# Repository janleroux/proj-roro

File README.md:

# RORO10

## Overview
The LERU Roro v1.0 is a small wireless transceiver module offers a comprehensive mix of long range, low power consumption and secure data transmission.It is designed to facilitate developers to quickly move the same platform they use for prototyping to industrial level LoRa and IoT solutions. It offers all the core functions that will solve 99% of the requirements to turn an idea to reality. It is easy to program, create and connect your things everywhere. 

The Roro wireless part is based on a RFM95 module which allows the user to send data and reach extremely long ranges at low data-rates. It provides ultra-long range spread spectrum communication and high interference immunity whilst minimising current consumption. It targets professional wireless sensor network applications such as irrigation systems, smart metering, smart cities, smartphone detection, building automation, to name a few.

Roro's mcu part use an ESP32 module from Espressif Systems. The ESP32 is a well known, widely used ultra-low-power microcontroller that incorporate connectivity options such as Wi-Fi and Bluetooth. It offers two CPU cores that can be individually controlled,and the CPU clock frequency is adjustable from 80 MHz to 240 MHz. The chip also has a low-powerco-processor that can be used instead of the CPU to save power while performing tasks that do not require muchcomputing power, such as monitoring of peripherals. ESP32 integrates a rich set of peripherals, ranging fromcapacitive touch sensors, Hall sensors, SD card interface, Ethernet, high-speed SPI, UART, I²S and I²C

[Roro Wiki](https://github.com/janleroux/leru-roro/wiki)

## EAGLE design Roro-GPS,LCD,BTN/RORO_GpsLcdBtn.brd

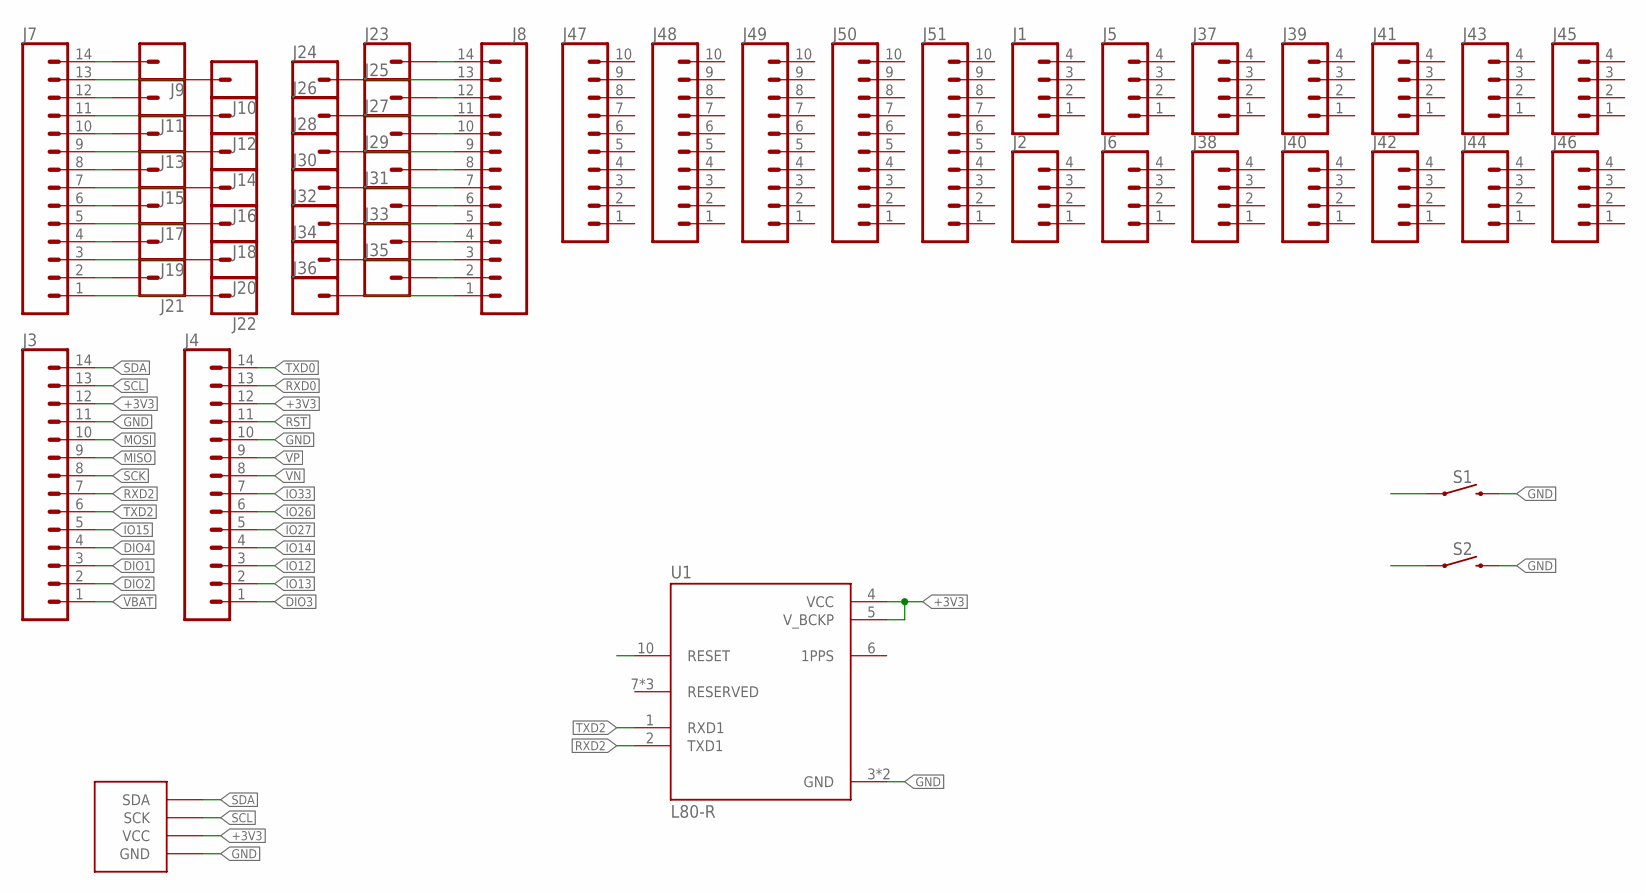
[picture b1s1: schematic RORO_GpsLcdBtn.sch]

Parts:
J1, J2, J5, J6, J37, J38, J39, J40, J41, J42, J43, J44, J45, J46: CONN_041X04_NO_SILK; 1X04_NO_SILK
J3, J4, J7, J8: CONN_14NO_SILK; 1X14_NO_SILK
J9, J10, J11, J12, J13, J14, J15, J16, J17, J18, J19, J20, J21, J22, J23, J24, J25, J26, J27, J28, J29, J30, J31, J32, J33, J34, J35, J36: CONN_01PTH_NO_SILK_KIT; 1X01NS_KIT
J47, J48, J49, J50, J51: CONN_10NO_SILK_PTH_FEMALE; 1X10_NO_SILK
S1, S2: MOMENTARY-SWITCH-SPST-SMD-6.0X3.5MM; TACTILE_SWITCH_SMD_6.0X3.5MM
U1: L80-R; XCVR_L80-R
U$1: 128X64_I2COLED

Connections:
+3V3: J3.12, J4.12, U1.4 (VCC), U1.5 (V_BCKP), U$1.P$3 (VCC)
DIO1: J3.3
DIO2: J3.2
DIO3: J4.1
DIO4: J3.4
GND: J3.11, J4.10, S1.2, S2.2, U1.3 (GND), U1.12 (GND), U$1.P$4 (GND)
IO12: J4.3
IO13: J4.2
IO14: J4.4
IO15: J3.5
IO26: J4.6
IO27: J4.5
IO33: J4.7
MISO: J3.9
MOSI: J3.10
unnamed: J7.14, J9.1
unnamed: J7.13, J10.1
unnamed: J7.12, J11.1
unnamed: J7.11, J12.1
unnamed: J7.10, J13.1
unnamed: J7.9, J14.1
unnamed: J7.8, J15.1
unnamed: J7.7, J16.1
unnamed: J7.6, J17.1
unnamed: J7.5, J18.1
unnamed: J7.4, J19.1
unnamed: J7.3, J20.1
unnamed: J7.2, J21.1
unnamed: J7.1, J22.1
unnamed: J8.14, J23.1
unnamed: J8.13, J24.1
unnamed: J8.12, J25.1
unnamed: J8.11, J26.1
unnamed: J8.10, J27.1
unnamed: J8.9, J28.1
unnamed: J8.8, J29.1
unnamed: J8.7, J30.1
unnamed: J8.6, J31.1
unnamed: J8.5, J32.1
unnamed: J8.4, J33.1
unnamed: J8.3, J34.1
unnamed: J8.2, J35.1
unnamed: J8.1, J36.1
RST: J4.11
RXD0: J4.13
RXD2: J3.7, U1.2 (TXD1)
SCK: J3.8
SCL: J3.13, U$1.P$2 (SCK)
SDA: J3.14, U$1.P$1 (SDA)
TXD0: J4.14
TXD2: J3.6, U1.1 (RXD1)
VBAT: J3.1
VN: J4.8
VP: J4.9

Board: 2 copper layers, 55 parts (0 on the bottom side), 34 nets, no tracks yet.

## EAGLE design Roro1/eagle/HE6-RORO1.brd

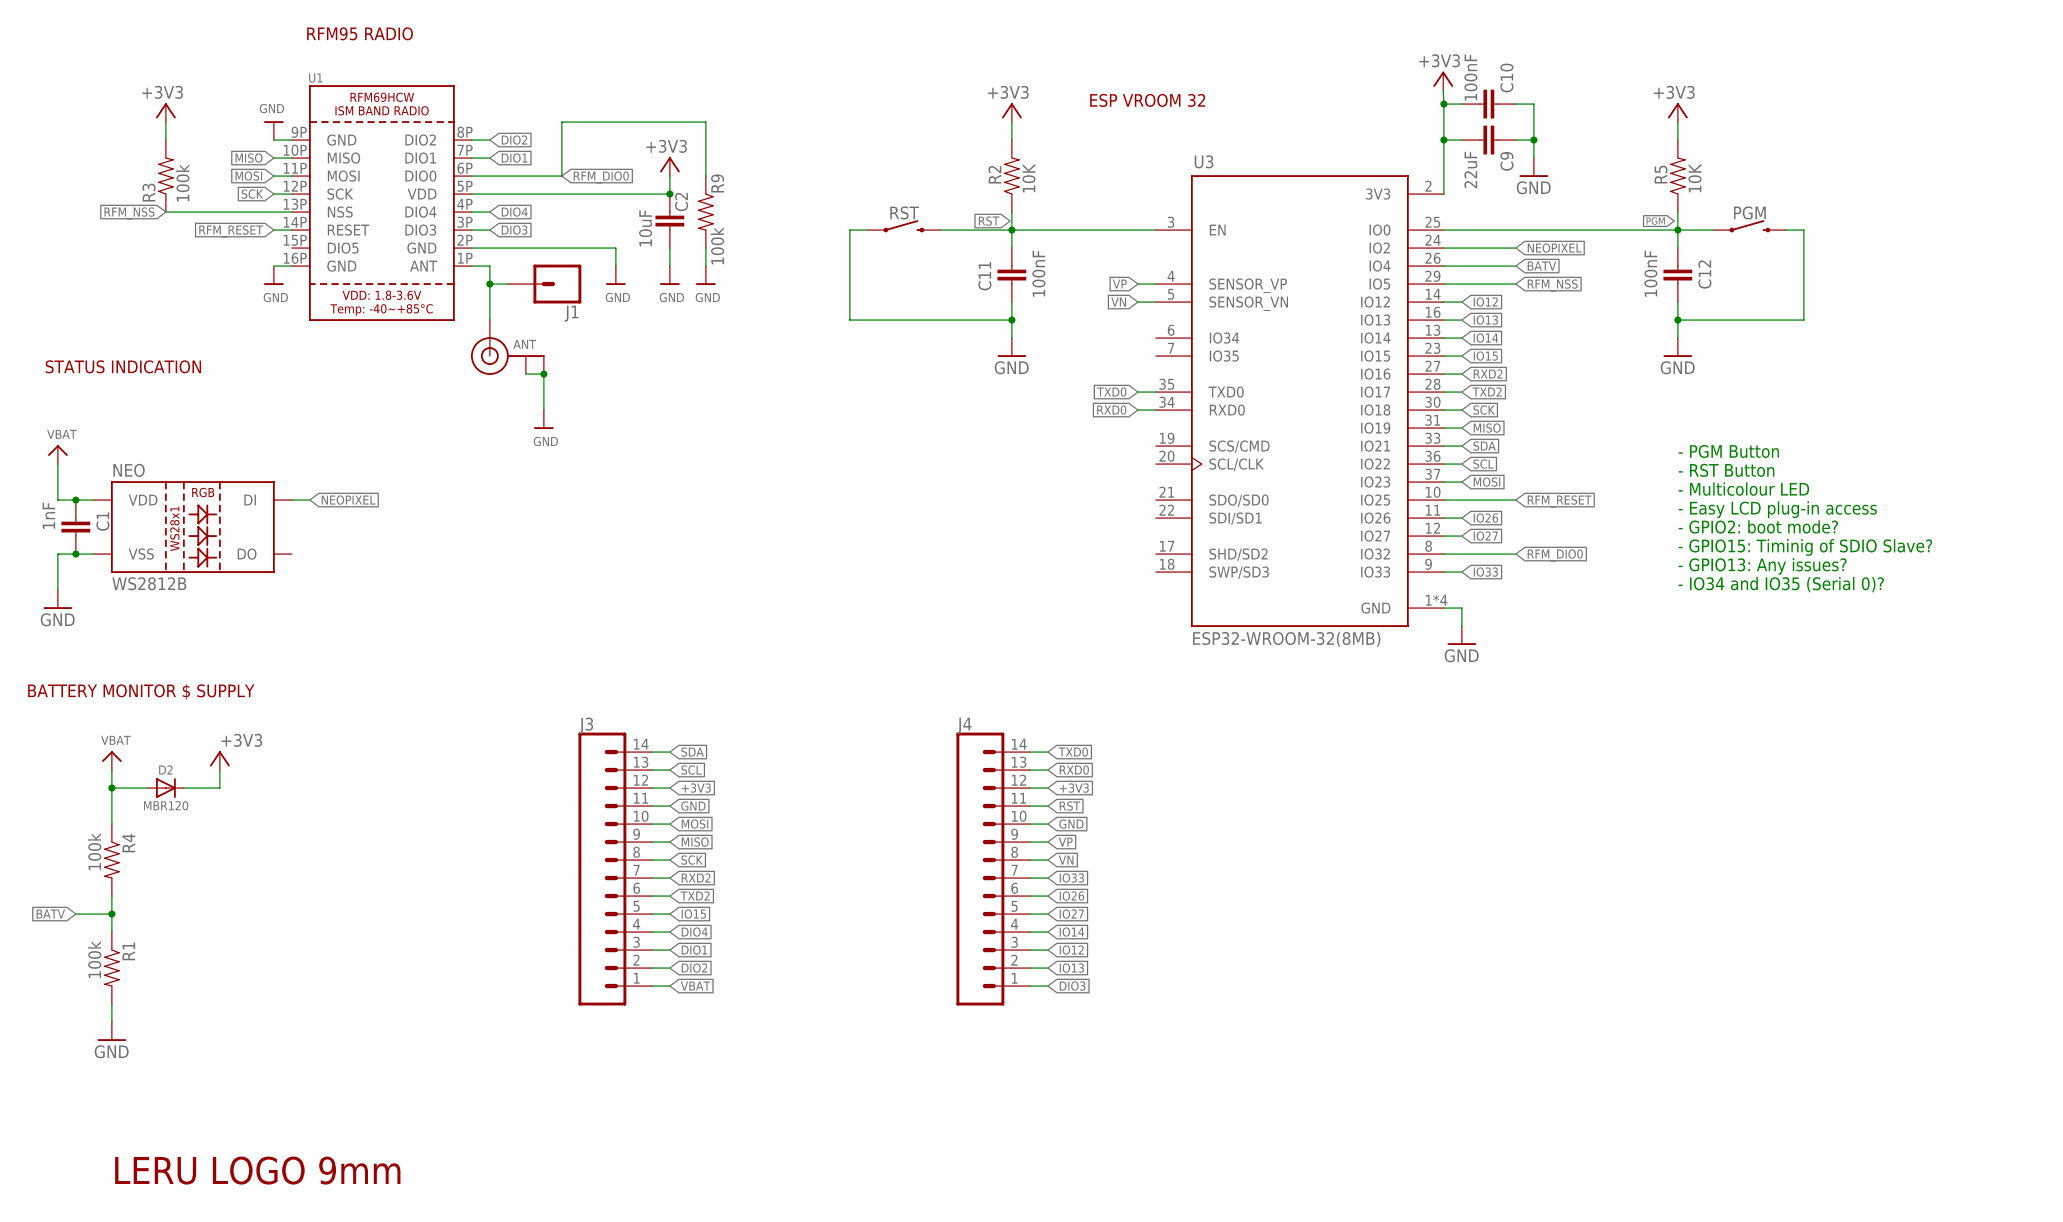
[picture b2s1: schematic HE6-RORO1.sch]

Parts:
ANT: MICROBUILDER_ANTENNA_U.FL; MICROBUILDER_U.FL
C1: 1nF; CAP
C2: 10uF; CAP
C9: 22uF; CAP
C10, C11, C12: 100nF; CAP
D2: MBR120; DIODE
J1: CONN_01PTH_NO_SILK_YES_STOP; 1X01_NO_SILK
J3, J4: CONN_14NO_SILK; 1X14_NO_SILK
NEO: WS2812B
PGM: MOMENTARY-SWITCH-SPST-SMD-RIGHT-ANGLE; TACTILE_SWITCH_SMD_RIGHT_ANGLE
R1, R3, R4, R9: 100k; RES
R2, R5: 10K; RES
RST: MOMENTARY-SWITCH-SPST-SMD-RIGHT-ANGLE; TACTILE_SWITCH_SMD_RIGHT_ANGLE
U1: RFM69HCW_SMT; RFMHCW_SMT
U3: ESP32-WROOM-32(8MB); MODULE_ESP32-WROOM-32(8MB)
U$9: LERU_LOGO_9MM

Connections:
+3V3: C2.1, C9.2, C10.2, D2.1 (C), J3.12, J4.12, R2.2, R3.2, R5.2, U1.5P (VDD), U3.2 (3V3)
BATV: R1.1, R4.2, U3.26 (IO4)
DIO1: J3.3, U1.7P (DIO1)
DIO2: J3.2, U1.8P (DIO2)
DIO3: J4.1, U1.3P (DIO3)
DIO4: J3.4, U1.4P (DIO4)
GND: ANT.1 (GND), ANT.2 (GND), C1.1, C2.2, C9.1, C10.1, C11.1, C12.1, J3.11, J4.10, NEO.3 (VSS), PGM.2, R1.2, R9.2, RST.1, U1.2P (GND), U1.9P (GND), U1.16P (GND), U3.1 (GND), U3.15 (GND), U3.38 (GND), U3.39 (GND)
IO12: J4.3, U3.14 (IO12)
IO13: J4.2, U3.16 (IO13)
IO14: J4.4, U3.13 (IO14)
IO15: J3.5, U3.23 (IO15)
IO26: J4.6, U3.11 (IO26)
IO27: J4.5, U3.12 (IO27)
IO33: J4.7, U3.9 (IO33)
MISO: J3.9, U1.10P (MISO), U3.31 (IO19)
MOSI: J3.10, U1.11P (MOSI), U3.37 (IO23)
unnamed: ANT.3 (SIGNAL), J1.1, U1.1P (ANT)
NEOPIXEL: NEO.4 (DI), U3.24 (IO2)
PGM: C12.2, PGM.1, R5.1, U3.25 (IO0)
RFM_DIO0: R9.1, U1.6P (DIO0), U3.8 (IO32)
RFM_NSS: R3.1, U1.13P (NSS), U3.29 (IO5)
RFM_RESET: U1.14P (RESET), U3.10 (IO25)
RST: C11.2, J4.11, R2.1, RST.2, U3.3 (EN)
RXD0: J4.13, U3.34 (RXD0)
RXD2: J3.7, U3.27 (IO16)
SCK: J3.8, U1.12P (SCK), U3.30 (IO18)
SCL: J3.13, U3.36 (IO22)
SDA: J3.14, U3.33 (IO21)
TXD0: J4.14, U3.35 (TXD0)
TXD2: J3.6, U3.28 (IO17)
VBAT: C1.2, D2.2 (A), J3.1, NEO.1 (VDD), R4.1
VN: J4.8, U3.5 (SENSOR_VN)
VP: J4.9, U3.4 (SENSOR_VP)

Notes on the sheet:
RFM95 RADIO
ESP VROOM 32
BATTERY MONITOR $ SUPPLY
- PGM Button - RST Button - Multicolour LED - Easy LCD plug-in access - GPIO2: boot mode? - GPIO15: Timinig of SDIO Slave? - GPIO13: Any issues? - IO34 and IO35 (Serial 0)?
STATUS INDICATION

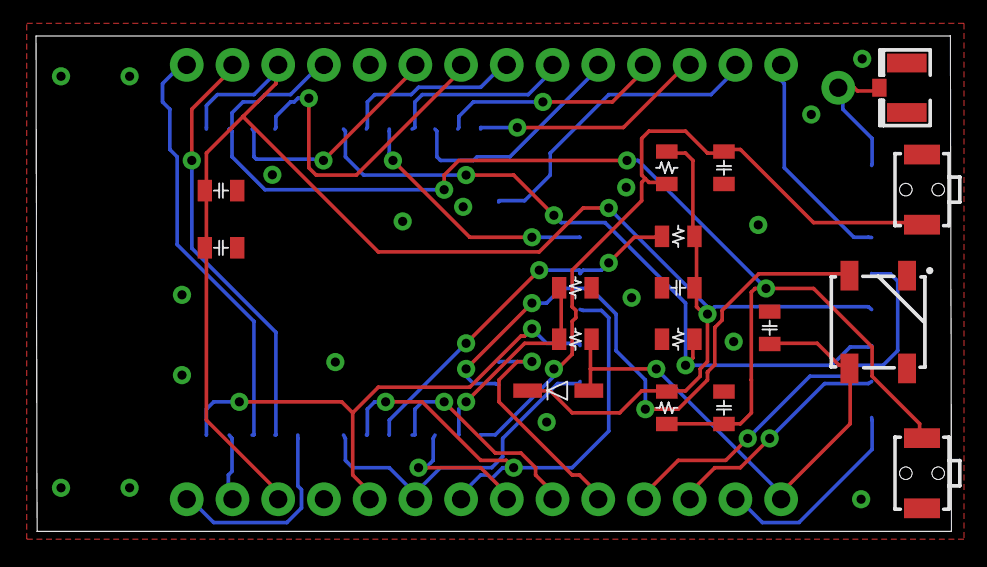
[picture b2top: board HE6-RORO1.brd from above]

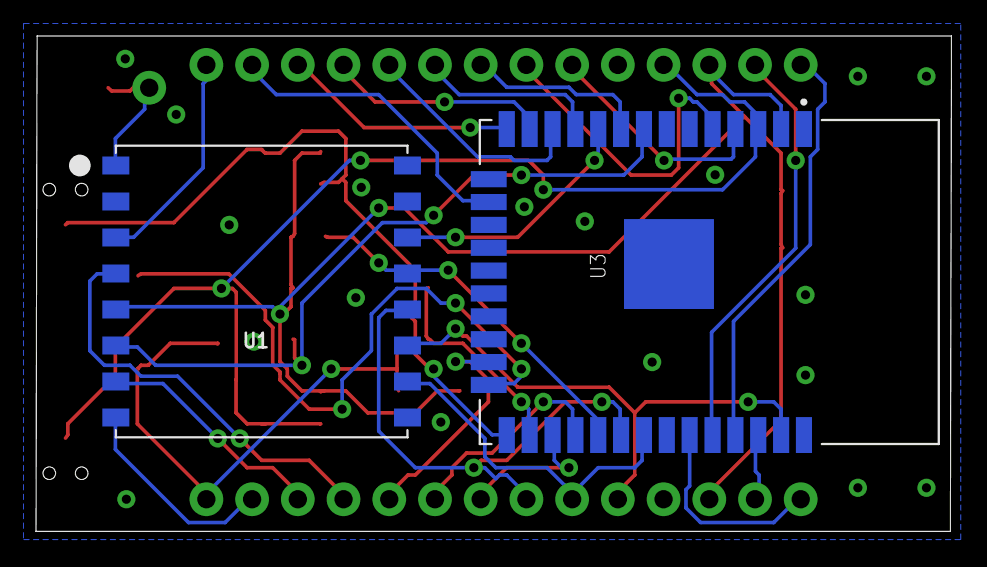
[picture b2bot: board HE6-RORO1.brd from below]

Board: 2 copper layers, 50.9 x 27.5 mm, 23 parts (2 on the bottom side), 33 nets.

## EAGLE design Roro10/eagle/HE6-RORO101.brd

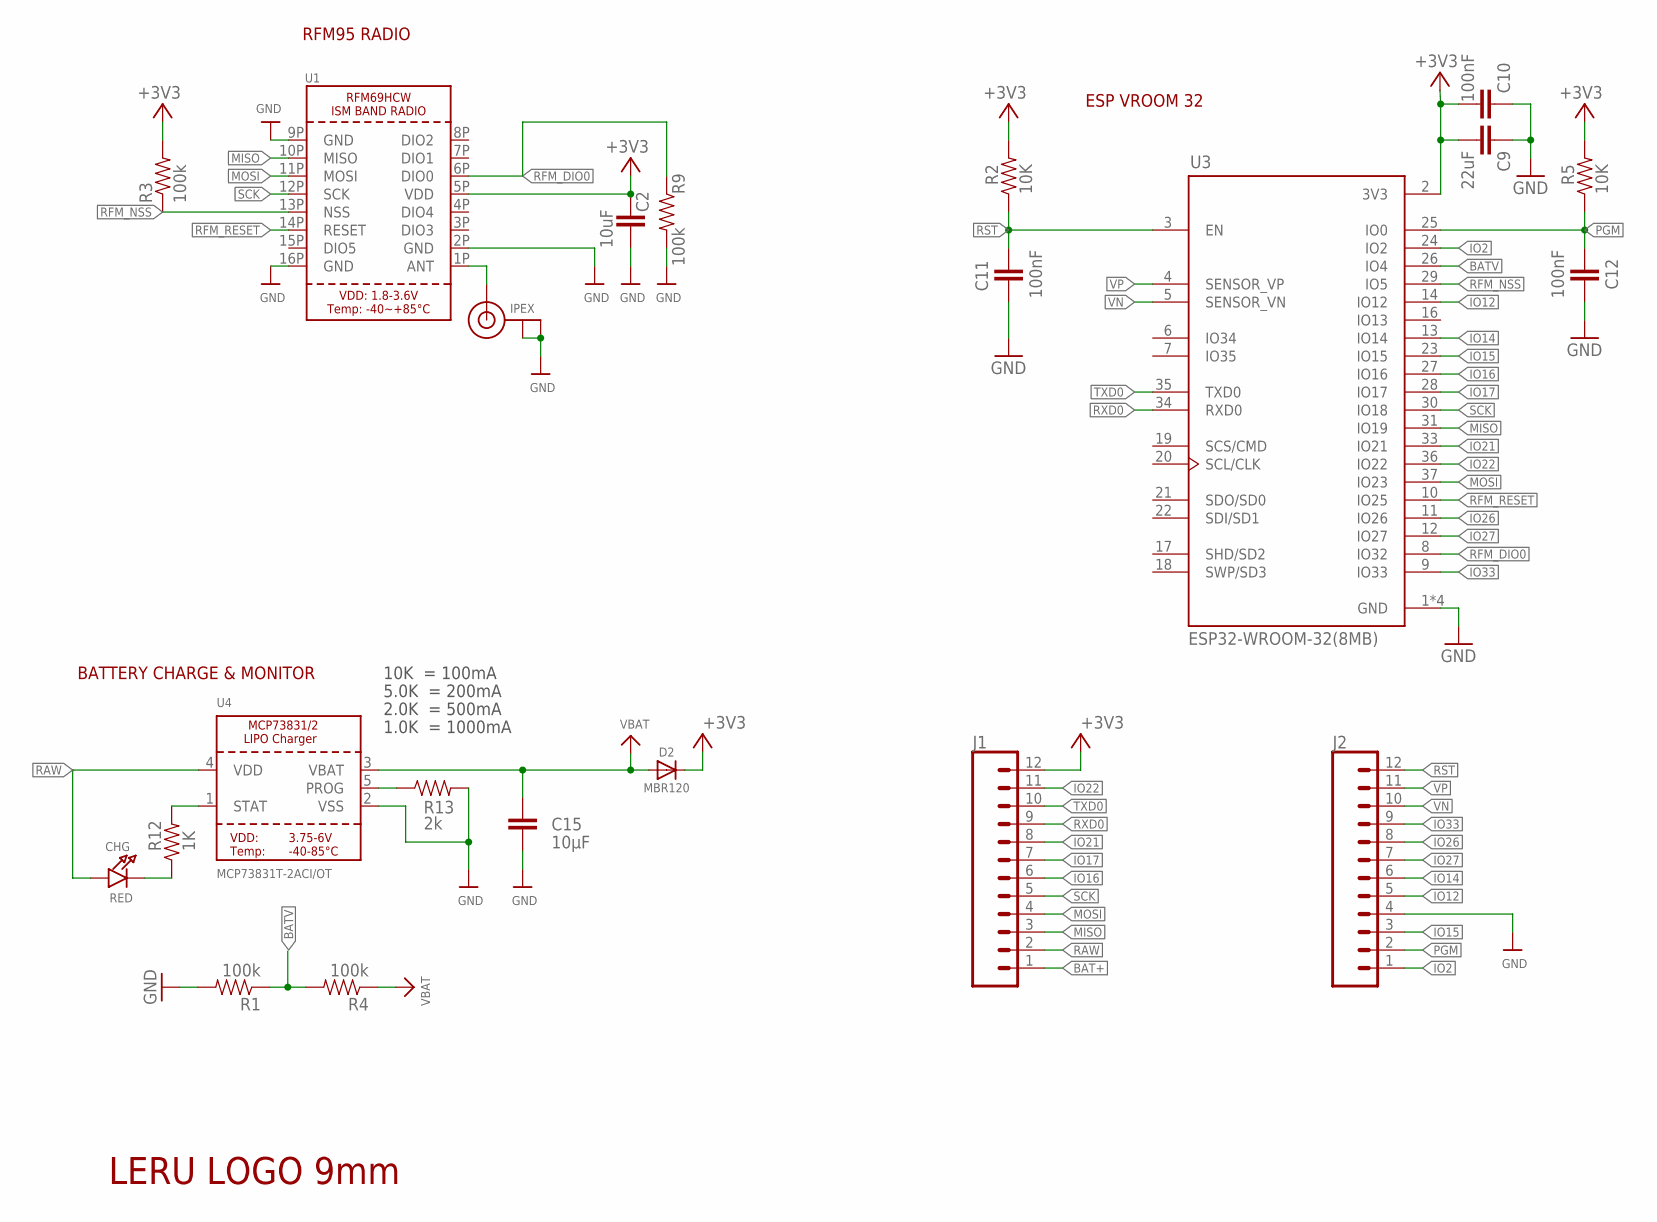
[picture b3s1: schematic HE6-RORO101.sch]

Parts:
C2: 10uF; CAP
C9: 22uF; CAP
C10, C11, C12: 100nF; CAP
C15: 10µF; CAP
CHG: RED; CHIPLED_0805_NOOUTLINE
D2: MBR120; DIODE
IPEX: MICROBUILDER_ANTENNA_U.FL; MICROBUILDER_U.FL
J1, J2: CONN_12LONGPADS; 1X12_LONGPADS
R1, R3, R4, R9: 100k; RES
R2, R5: 10K; RES
R12: 1K; RES
R13: 2k; RES
U1: RFM69HCW_SMT; RFMHCW_SMT
U3: ESP32-WROOM-32(8MB); MODULE_ESP32-WROOM-32(8MB)
U4: MCP73831T-2ACI/OT; SOT23-5
U$9: LERU_LOGO_9MM

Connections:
+3V3: C2.1, C9.2, C10.2, D2.1 (C), J1.12, R2.2, R3.2, R5.2, U1.5P (VDD), U3.2 (3V3)
BAT+: C15.1, D2.2 (A), J1.1, R4.1, U4.3 (VBAT)
BATV: R1.1, R4.2, U3.26 (IO4)
GND: C2.2, C9.1, C10.1, C11.1, C12.1, C15.2, IPEX.1 (GND), IPEX.2 (GND), J2.4, R1.2, R9.2, R13.2, U1.2P (GND), U1.9P (GND), U1.16P (GND), U3.1 (GND), U3.15 (GND), U3.38 (GND), U3.39 (GND), U4.2 (VSS)
IO2: J2.1, U3.24 (IO2)
IO12: J2.5, U3.14 (IO12)
IO14: J2.6, U3.13 (IO14)
IO15: J2.3, U3.23 (IO15)
IO16: J1.6, U3.27 (IO16)
IO17: J1.7, U3.28 (IO17)
IO21: J1.8, U3.33 (IO21)
IO22: J1.11, U3.36 (IO22)
IO26: J2.8, U3.11 (IO26)
IO27: J2.7, U3.12 (IO27)
IO33: J2.9, U3.9 (IO33)
MISO: J1.3, U1.10P (MISO), U3.31 (IO19)
MOSI: J1.4, U1.11P (MOSI), U3.37 (IO23)
unnamed: IPEX.3 (SIGNAL), U1.1P (ANT)
unnamed: CHG.C, R12.1
unnamed: R12.2, U4.1 (STAT)
unnamed: R13.1, U4.5 (PROG)
PGM: C12.2, J2.2, R5.1, U3.25 (IO0)
RAW: CHG.A, J1.2, U4.4 (VDD)
RFM_DIO0: R9.1, U1.6P (DIO0), U3.8 (IO32)
RFM_NSS: R3.1, U1.13P (NSS), U3.29 (IO5)
RFM_RESET: U1.14P (RESET), U3.10 (IO25)
RST: C11.2, J2.12, R2.1, U3.3 (EN)
RXD0: J1.9, U3.34 (RXD0)
SCK: J1.5, U1.12P (SCK), U3.30 (IO18)
TXD0: J1.10, U3.35 (TXD0)
VN: J2.10, U3.5 (SENSOR_VN)
VP: J2.11, U3.4 (SENSOR_VP)

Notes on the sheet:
RFM95 RADIO
ESP VROOM 32
10K = 100mA
5.0K = 200mA
2.0K = 500mA
1.0K = 1000mA
BATTERY CHARGE & MONITOR

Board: 2 copper layers, 23 parts (0 on the bottom side), 32 nets, no tracks yet.

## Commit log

2022-08-22 ping-pong test
2022-09-26 roro2 pcb corrections + bcdrotary sketch

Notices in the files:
parts and their libraries:
SparkFun-Connectors: Licensing: Creative Commons ShareAlike 4.0 International - https://creativecommons.org/licenses/by-sa/4.0
microbuilder: This work is placed in the public domain, and may be freely used for commercial and non-commercial work with the following conditions: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
